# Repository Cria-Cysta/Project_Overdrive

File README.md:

# Project overdrive

Overdrive Model Ver. 21B20

>中文版介绍请点击[这里](https://shimo.im/docs/xqpTWwy3x8qtTTDj/)。

### What is it?

It's a game controller which designed for SDVX E-cloud, USC, KSM.

Compared with other controllers, it has a compromise size. When I designing this controller, I have tried to find a size to adapt to as many hand shapes as possible. And that it is.

### Features

It have bigger size to allow you could easily touch the BT-button. 3D-printed BT-buttons make the   finger contact area larger than standard keyboard key. Slightly inward moved position of FX-button relaxed your thumbs when you're playing.

### Materials

In order to make this controller, you'll need: 

1. Cover 3D-printed parts ×1
2. Middle bracket 3D-printed parts ×1
3. Lower lid 3D-printed parts ×1
4. BT-button 3D-printed parts ×4
5. EC11 rotary encoder ×2
6. PCB ×1 (thickness: 1.6mm)
7. Keyboard axis ×7
8. Satellite axis ×8
9. Pro micro development board ×1, With solder pins
10. Several GB M2×18 countersunk screw 
11. 20cm Micro USB male to female Type-C converter ×1.
12. Φ25mm knob ×2
13. 1u×1u DSA Keycap ×1
14. 1u×1.75u DSA Keycap ×2
15. Φ10mm mat ×4

In addition, you also need to prepare solder, flux, electric soldering iron and other tools used to solder the circuit board, as well as a small Phillips screwdriver. Because 3D-printed parts may have dimensional tolerances, prepare sandpaper as appropriate. 

### Guide

In production, stay tuned ;-)

Because it is designed to be easy to assemble, you can try to assemble it yourself.

### About design

Q: Why is the appearance very round, despite the use of 3D printing, there is no design of extra protrusions?
A: When playing SDVX E-cloud or other laser-shoot-type games, due to the variety of gameplay requirements, if you are not familiar with the chart or playing the difficult music chart, it may lead to violent operations that vary from person to person. The smooth appearance can maximize the protection of the user's hands when playing.

Q: Why are there chamfers near the buttons?
A: Since this controller is a miniaturized controller, the size standard part refers to a part that made for a mechanical keyboard. The specifications of the BT button 2U*2U are not guaranteed to fit everyone's hands. Therefore, in order to prevent the nails from reaching the gap and being caught, all buttons are designed with chamfers. 

Q: Why did the position of the FX button move inward?
A: The two FX buttons move inward for convenience. The design of the controller is for ease of use or to restore the feel of the arcade. These two design directions will inevitably have contradictions in some aspects. The inward movement of the FX button can reduce the accumulation of fatigue caused by long-term play under the design of the hand console, and it can also take care of players with relatively short finger lengths.

Q: Why is there no LED light like other miniaturized controllers?
A: Future versions consider adding this feature.

Q: Since the design is based on the size of the mechanical keyboard, why does the controller use non-standard BT keys?
A: The shaft of the existing 2U*2U keys on the market is not in the center. Whether it is adding a shaft body or filling the remaining slots with a satellite shaft, it will seriously affect the feel of the button and the force feedback. 

### Others

This work is licensed under a Creative Commons Attribution-NonCommercial-ShareAlike 4.0 International License.

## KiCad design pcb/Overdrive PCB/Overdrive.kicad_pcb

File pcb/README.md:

# PCB files

Please open it with KiCad.

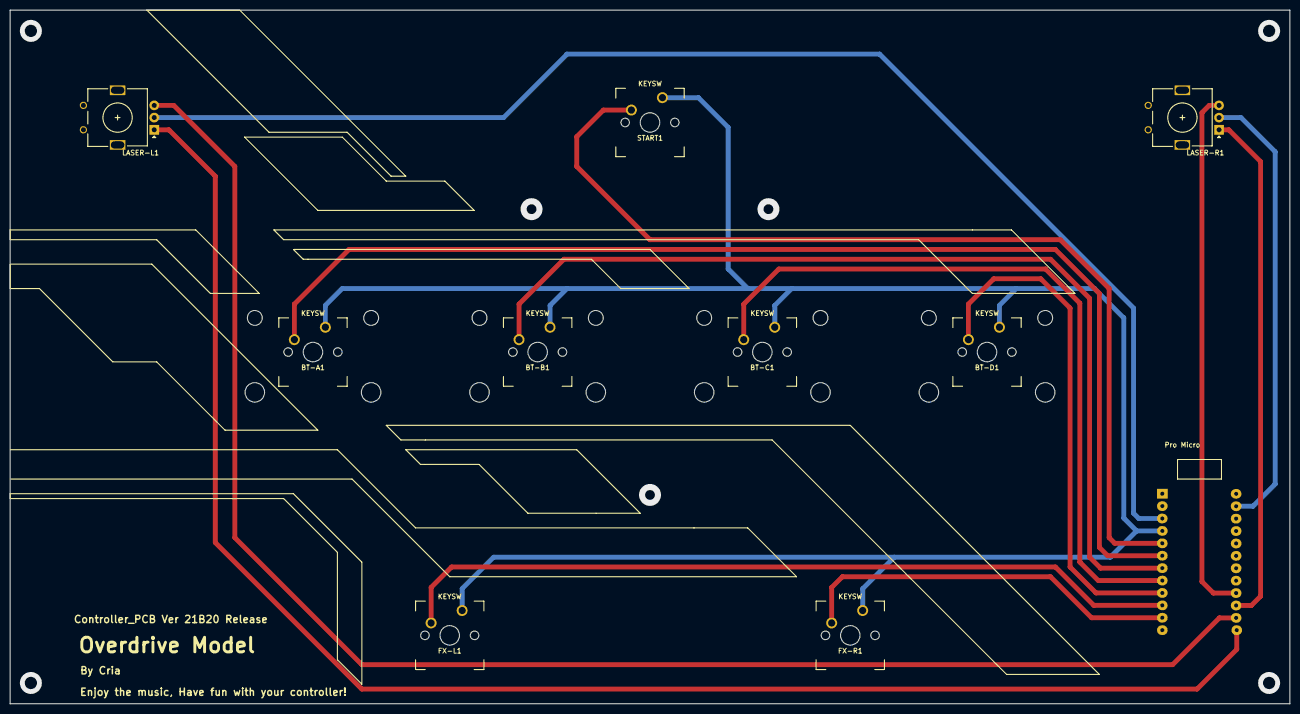
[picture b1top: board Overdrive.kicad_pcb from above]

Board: 2 copper layers, 262.0 x 142.0 mm, 10 parts (0 on the bottom side), 14 nets.

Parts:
BT-A1: KEYSW; MXOnly-2U-NoLED
BT-B1: KEYSW; MXOnly-2U-NoLED
BT-C1: KEYSW; MXOnly-2U-NoLED
BT-D1: KEYSW; MXOnly-2U-NoLED
FX-L1: KEYSW; MXOnly-1.75U-NoLED
FX-R1: KEYSW; MXOnly-1.75U-NoLED
LASER-L1: EC11_without_switch; RotaryEncoder_Alps_EC11E_Vertical_H20mm
LASER-R1: EC11_without_switch; RotaryEncoder_Alps_EC11E_Vertical_H20mm
START1: KEYSW; MXOnly-1U-NoLED
U1: ProMicro; SparkfunPromicro

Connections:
unnamed: BT-A1.1, U1.3
unnamed: BT-A1.2, BT-B1.2, BT-C1.2, BT-D1.2, FX-L1.2, FX-R1.2, START1.2, U1.GND2
unnamed: BT-B1.1, U1.4
unnamed: BT-C1.1, U1.5
unnamed: BT-D1.1, U1.6
unnamed: FX-L1.1, U1.7
unnamed: FX-R1.1, U1.8
unnamed: LASER-L1.A, U1.10
unnamed: LASER-L1.B, U1.16
unnamed: LASER-L1.C, U1.GND1
unnamed: LASER-R1.A, U1.14
unnamed: LASER-R1.B, U1.15
unnamed: LASER-R1.C, U1.GND3
unnamed: START1.1, U1.2

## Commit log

2021-02-20 main
2021-02-20 Ver. 21B20
